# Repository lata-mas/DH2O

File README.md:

# Dispositivo H2O

Este dispositivo se realizó gracias al apoyo del proyecto UNAM-PAPIIT IT103023.

Este dispositivo se desarrollo con el objetivo de medir la cantidad de agua que se consume en un edificio y poder implementar medidas para evitar consumos excesivos de este valioso recurso.

El dispositivo funciona con un módulo NodeMCU Lolin V3→ESP8266-12E, permitiendo interpretar los datos que recolecta el sensor YF-S201 (sensor de caudal de agua), el microcontrolador  permite interpretar datos y después enviarlos a través de Wifi a una plataforma de imternet. La ventaja más significativa es precisamente esa, que el módulo tiene wifi, permitiendo que pueda enviar datos en tiempo real a diferentes plataformas de visualización, ademas de su reducido tamaño.

A continuación se muestra el esquema general del dispositivo y algunos de sus componetes principales:

1. Sensor de caudal
2. Divisor de voltaje
3. LM324

[Diagrama electrico](https://github.com/Dispositivos-Edificio-Bioclimatico/DH2O/blob/master/Diagramas/DispositivoH2O1Esquem%C3%A1tico.pdf)

## 1. Elementos del repositorio
-  #### En [**docs**](https://github.com/Dispositivos-Edificio-Bioclimatico/DH2O/tree/master/Documentacion) encontramos
	-  Lista de materiales y costos
	-  Manual de operación
	-  Fichas técnicas o datasheet de los módulos, sensores y componentes usados
	- Documento de errores, soluciones y recomendaciones

-  #### En [**diagramas**](https://github.com/Dispositivos-Edificio-Bioclimatico/DH2O/tree/master/Diagramas) encontramos
	- Pictograma de conexión
	- Esquemático de conexión
	
-  #### En [**codigo**](https://github.com/Dispositivos-Edificio-Bioclimatico/DH2O/tree/master/codigo) encontramos
	- Códigos completos
	- Librerías a usar.
	- Explicación.

-  #### En [**Imagenes**](https://github.com/Dispositivos-Edificio-Bioclimatico/Sistema_medicion_apertura_ventanas/tree/main/notebook) encontramos
	-  Imagenes usadas en el repositorio

-  #### En [**carcasa**](https://github.com/Dispositivos-Edificio-Bioclimatico/DH2O/tree/master/Diagramas) encontramos
	-  Planos CAD
	-  Archivos de diseño CAD
	-  Archivos STL para impresión 3D

### 2 Sobre los autores

|Nombre|Instituto/Organización|Email|
| ------------ | ------------ | ------------ |
|Luis Fernando De Olarte Delgado|UTEZ|ferdeod16@gmail.com|
|Marco Antonio Morales Lagunes|UTEZ|marcostony001@gmail.com|
|Julio César Landa López|UTEZ|landajulioc@gmail.com|
|Miguel Ángel Gaspar|ITZ|miguel97gaz@gmail.com|
|Escobar Escobar José Williams|ITE|escobarescobarwilliams@gmail.com|
|Guillermo Barrios del Valle|IER-UNAM|gbv@ier.unam.mx|
|Guillermo Ramírez Zúñiga|IER-UNAM|guraz@ier.unam.mx|
|Giovanni Velazquez Avilez||velazquezgio96@gmail.com|
|José Diego Salgado Nieto||salgadojosediego@gmail.com|

------------

# 3 Alcance

El dispositivo H2O tiene como alcance, en esta etapa, contar con toda la documentación necesaria para ser replicado de manera eficaz y eficientemente, después de ser trabajado por un grupo de personas se espera que el proyecto tenga todo lo que se necesita para que otras personas puedan entender el funcionamiento y requisitos de operación.

------------

### 4 Contacto primario

**Inv. A tiempo completo:** Dr. Guillermo Barrios del Valle

**Email:** gbv@ier.unam.mx

**Posdoc.:** Dr. Guillermo Ramírez Zúñiga

**Email:** guraz@ier.unam.mx

### Colaboradores

**Nombre:** Luis Fernando De Olarte Delgado

**Instituto:** Universidad Tecnológica Emiliano Zapata (UTEZ)

**Email:** ferdeod16@gmail.com

**Nombre:** Marco Antonio Morales Lagunes

**Instituto:** Universidad Tecnológica Emiliano Zapata (UTEZ)

**Email:** marcostony001@gmail.com

**Nombre:** Julio César Landa López

**Instituto:** Universidad Tecnológica Emiliano Zapata (UTEZ)

**Email:** landajulioc@gmail.com

**Nombre:** Miguel Ángel Gaspar

**Instituto:** Instituto Tecnológico de Zacatepec (ITZ)

**Email:** miguel97gaz@gmail.com

**Nombre:** Escobar Escobar José Williams

**Instituto:** Instituto Tecnológico de Ensenada (ITE)

**Email:** escobarescobarwilliams@gmail.com

**Nombre:** Salgado Nieto josé Diego
**Insituto** Universidad Tecnológica Emiliano Zapata (UTEZ)
**Email:** salgadojosediego@gmail.com

#### 5 Seguimiento de actividades del dispositivo H2O

|**Actividad**|**Tiempo estimado de ejecución**|**Referenciación**|
| :------------: | :------------: | :------------: |
|**1. Revisión de documentos existentes necesarios para operarlo de acuerdo a la CHECK-LIST**|2 h|[**°Documentación**](https://github.com/Dispositivos-Edificio-Bioclimatico/SensorH2O/tree/master/Documentacion) |
|   |   |   |
|**2. Verificar si cuenta con los materiales requeridos**|1/2 h|[**Materiales**](https://github.com/Dispositivos-Edificio-Bioclimatico/DH2O/tree/master/Documentacion/Materiales)|
|   |   |   |
|**3. Imprimir la carcasa en 3D (3 PARTES)**|16 h|[**Archivos STL**](https://github.com/Dispositivos-Edificio-Bioclimatico/DH2O/tree/master/carcasa)|
|   |   |   |
|**4. Leer el manual de operación para entender lo que se hará**|1 h|[**Manual**](https://github.com/Dispositivos-Edificio-Bioclimatico/DH2O/blob/master/Documentacion/Manuales/ManualDeOperacion.md)|
|   |   |   |
|**5. Entender los diagramas de conexión**|1/2 h|[**Diagramas**](https://github.com/Dispositivos-Edificio-Bioclimatico/DH2O/blob/master/Diagramas/H2O-Esquem%C3%A1tico_2023ver2-KiCad.pdf)|
|   |   |   |
|**6. Descargar e instalar el código completo (son 5 .py)**|1/2 h|[**Código H2O**](https://github.com/Dispositivos-Edificio-Bioclimatico/DH2O/tree/master/codigo)|
|   |   |   |
|**7. Ejecutar el código como primera prueba y asegurarse que funciona**|   |   |
|   |   |   |
|**8. Montar el dispositivo en el lugar requerido**|1 h|   |
|   |   |   |
|**9. Dejarlo operando durante 24 horas como prueba "Burn it"**|24 h|   |
|   |   |   |
|**10. Tiempo total apróximado:**|**3 días**|Dependerá de la habilidad y conocimientos que se tengan, puede llevar menos tiempo o más|

------------

### Thingsboard

Dashboard del dispositivo H2O en la plataforma de Thingsboard:

Miguel_H2O

Las credenciales para tener acceso se deberán solicitar con alguno de los doctores.

La web (Dashboard) se encuentra aquí:

[**Miguel_H2O**](http://iot.ier.unam.mx:8080/dashboard/5825dc60-059e-11eb-9c3f-d1ead9980bc3?publicId=0e7066c0-6e70-11e8-b1f3-991d62d050bd)

------------

# 6 Bibliografía

[1] Open Know-How
https://app.standardsrepo.com/MakerNetAlliance/OpenKnowHow/src/branch/master/1#a40dfa47-8bff-4e28-9338-3f808ddfe6ae

[2] Github
https://github.com/

[3] EasyEDA
https://easyeda.com/editor

[4] Fritzing
https://fritzing.org/

[5] DILLINGER
https://dillinger.io/

[6] M Editor.md
https://pandao.github.io/editor.md/en.html

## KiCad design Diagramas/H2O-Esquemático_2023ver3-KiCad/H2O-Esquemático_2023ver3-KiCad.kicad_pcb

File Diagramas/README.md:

##Diargramas del DH2O

En esta carpeta se presentan los diagramas.

Todo aquel documento qque represente como se construyó el dispositivo, diagramas de conexión, diagramas esequematicos y documentos CAD para su carcasa.
Los diagramas fueron realizados con el software libre KIcad, las carpetas presentan versiones de esquematicos y de pbc que muestran distintas formas de alimentación. Ambas versiones son funcionales, queda a elección del usuario cual usar.

En los directorios es posible encontrr los archivos gerber correspondientes para su  fabricación en PCB.

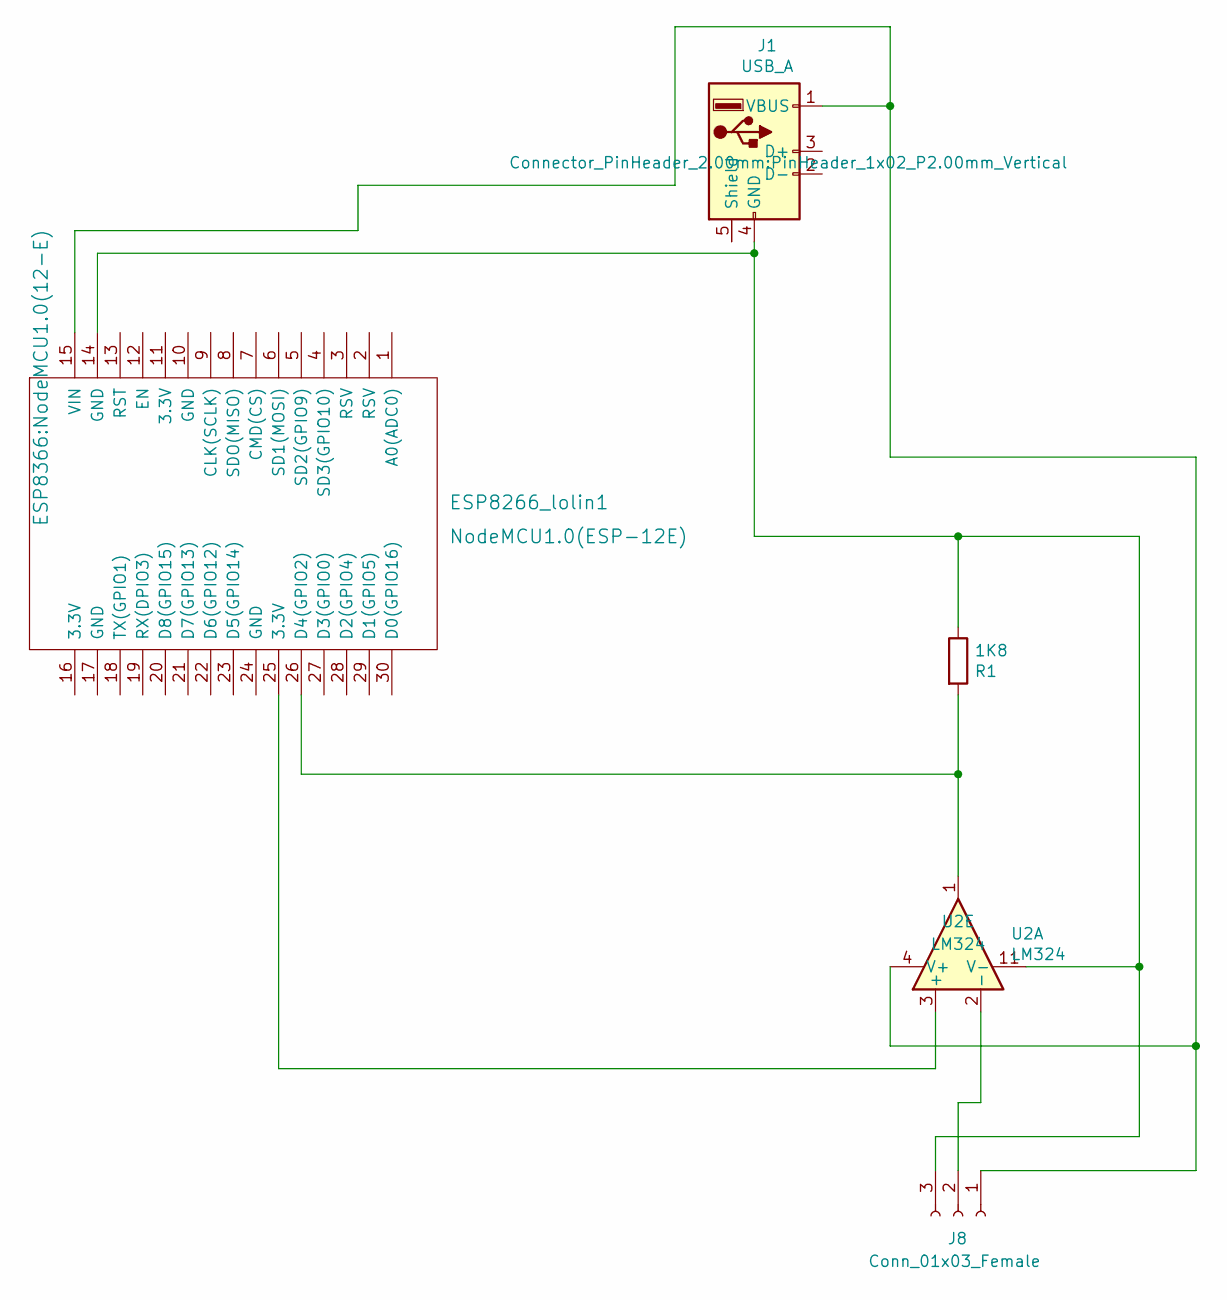
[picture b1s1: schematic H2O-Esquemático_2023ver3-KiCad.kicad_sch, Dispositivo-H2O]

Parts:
1K8: R1; R_Axial_DIN0207_L6.3mm_D2.5mm_P10.16mm_Horizontal
ESP8266_lolin1: NodeMCU1.0(ESP-12E); NodeMCU1.0(12-E)
J1: USB_A; PinHeader_1x02_P2.00mm_Vertical
J8: Conn_01x03_Female; TerminalBlock_4Ucon_1x03_P3.50mm_Vertical
U2: LM324; DIP-14_W7.62mm

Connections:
unnamed: 1K8.1, ESP8266_lolin1.14 (GND), J1.4 (GND), J8.3, U2.11 (V-)
unnamed: 1K8.2, ESP8266_lolin1.26 (D4(GPIO2)), U2.1
unnamed: ESP8266_lolin1.15 (VIN), J1.1 (VBUS), J8.1, U2.4 (V+)
unnamed: ESP8266_lolin1.25 (3.3V), U2.3 (+)
unnamed: J8.2, U2.2 (-)

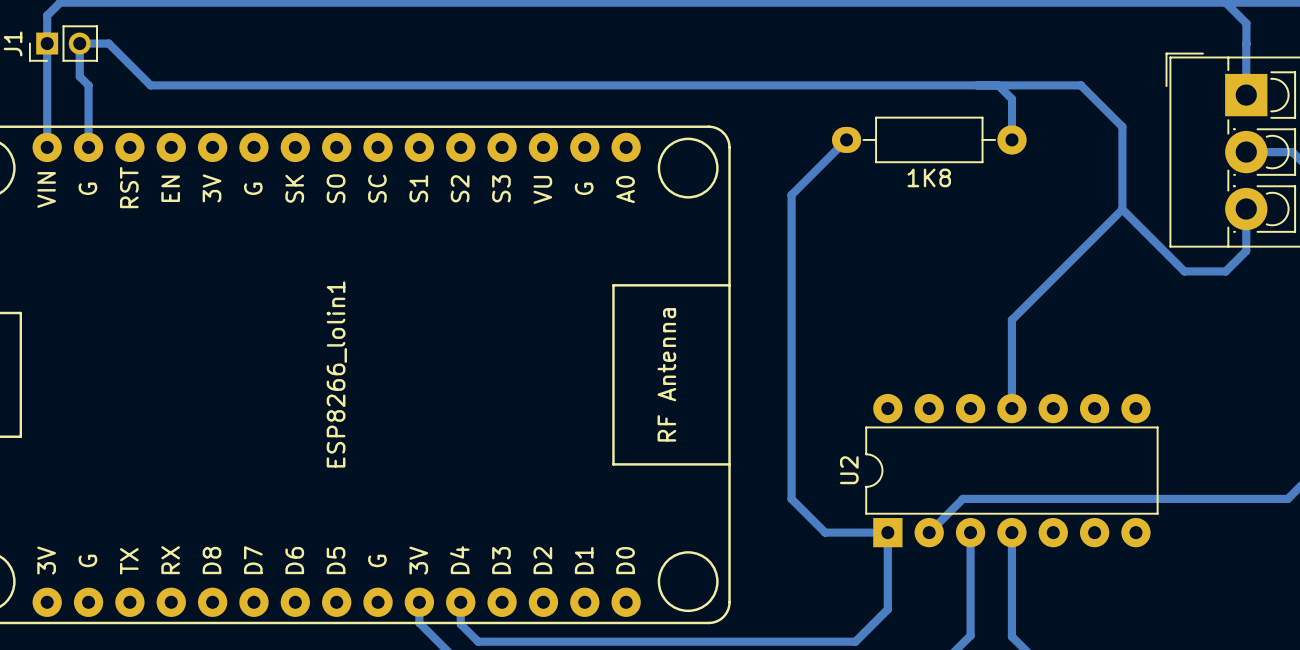
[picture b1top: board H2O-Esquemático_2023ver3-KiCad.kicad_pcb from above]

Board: 2 copper layers, 5 parts (0 on the bottom side), 5 nets.

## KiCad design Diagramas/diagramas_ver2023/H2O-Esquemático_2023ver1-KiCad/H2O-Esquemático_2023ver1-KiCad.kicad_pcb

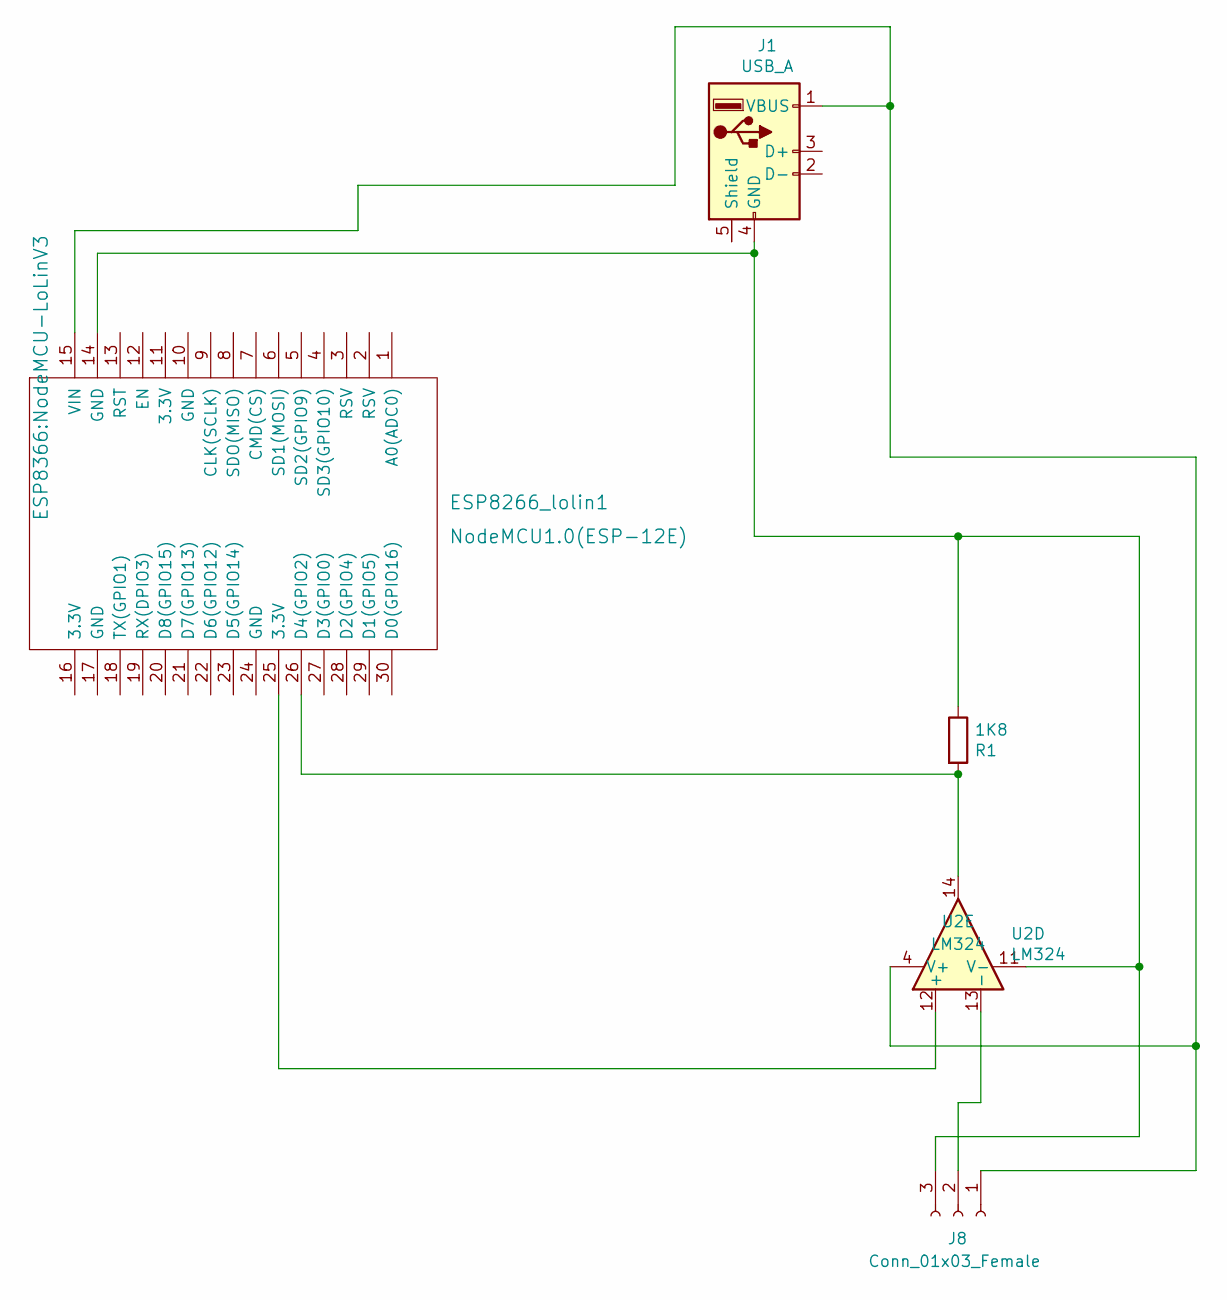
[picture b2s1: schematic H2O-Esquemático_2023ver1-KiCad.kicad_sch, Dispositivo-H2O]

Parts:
1K8: R1; R_Axial_DIN0207_L6.3mm_D2.5mm_P10.16mm_Horizontal
ESP8266_lolin1: NodeMCU1.0(ESP-12E); NodeMCU-LoLinV3
J1: USB_A; PinHeader_1x04_P1.27mm_Horizontal
J8: Conn_01x03_Female; TerminalBlock_Altech_AK300-3_P5.00mm
U2: LM324; DIP-14_W7.62mm

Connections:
unnamed: ESP8266_lolin1.25 (3.3V), U2.12 (+)
unnamed: 1K8.2, ESP8266_lolin1.26 (D4(GPIO2)), U2.14
unnamed: ESP8266_lolin1.15 (VIN), J1.1 (VBUS), J8.1, U2.4 (V+)
unnamed: 1K8.1, ESP8266_lolin1.14 (GND), J1.4 (GND), J8.3, U2.11 (V-)
unnamed: J8.2, U2.13 (-)

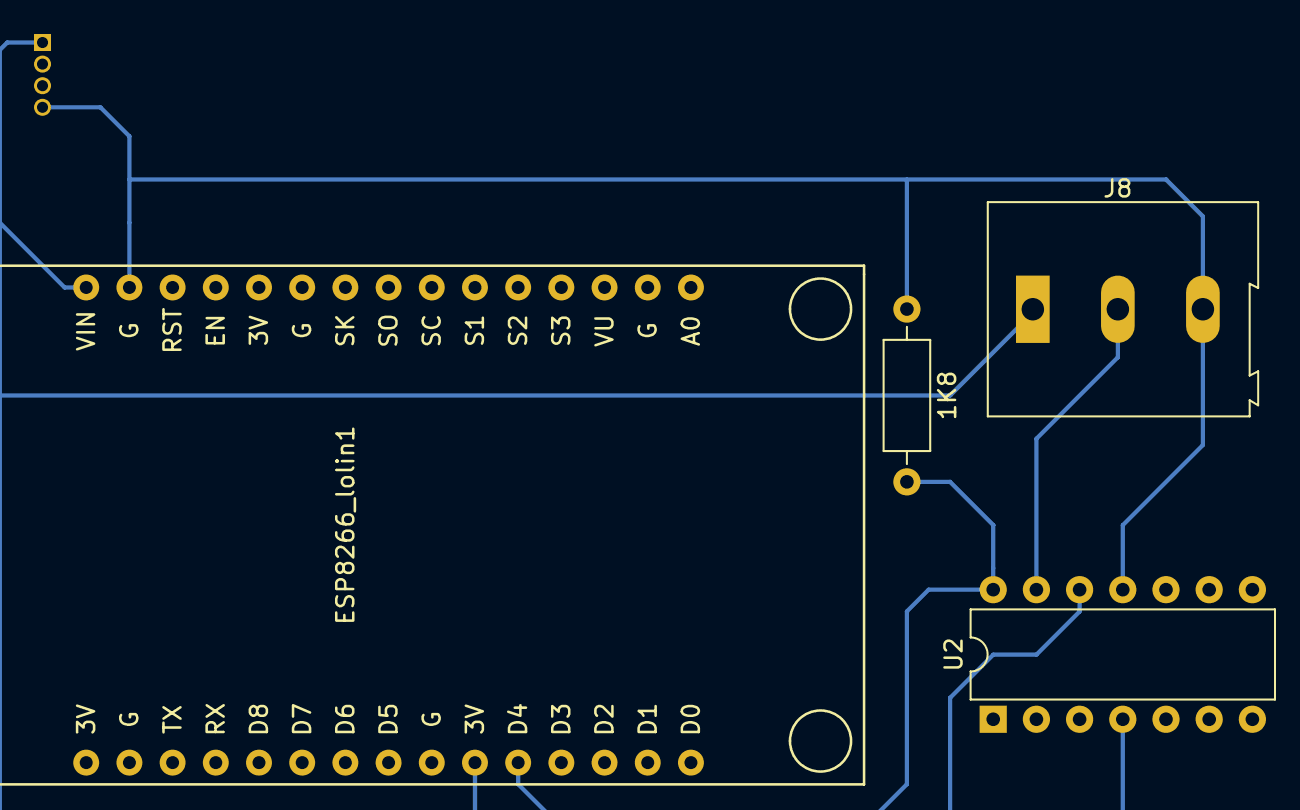
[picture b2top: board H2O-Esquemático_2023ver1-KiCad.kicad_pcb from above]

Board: 2 copper layers, 5 parts (1 on the bottom side), 5 nets.

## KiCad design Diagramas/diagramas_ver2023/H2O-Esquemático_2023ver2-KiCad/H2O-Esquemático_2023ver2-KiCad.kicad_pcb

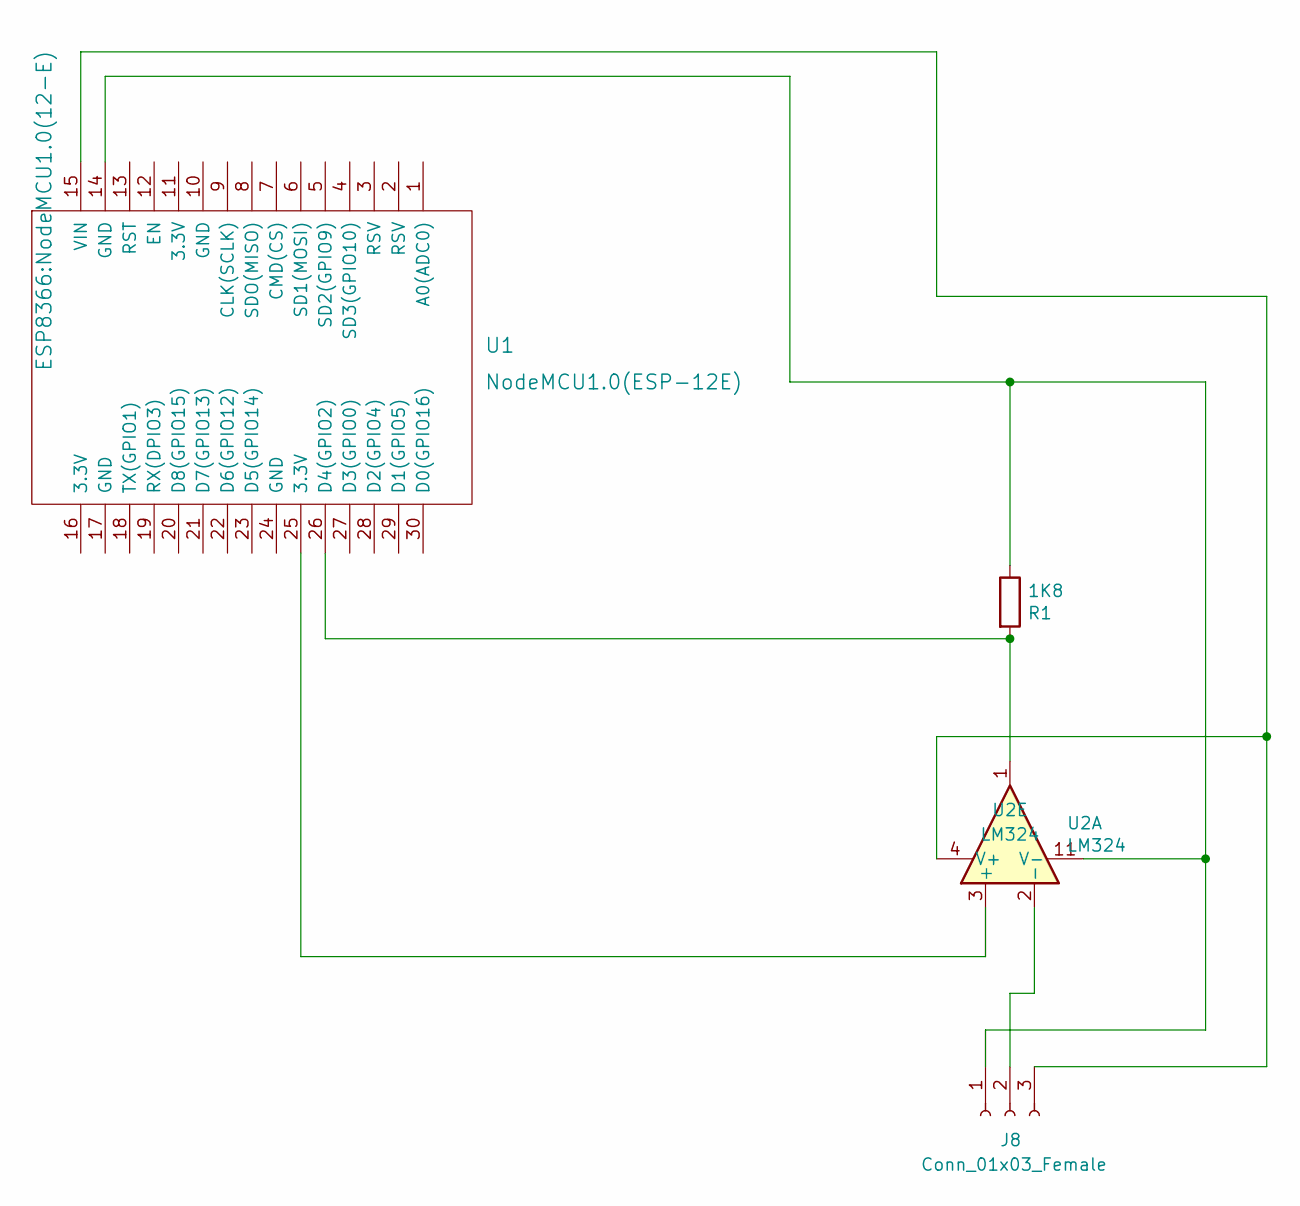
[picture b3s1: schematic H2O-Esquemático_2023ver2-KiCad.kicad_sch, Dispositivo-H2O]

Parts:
1K8: R1; R_Axial_DIN0207_L6.3mm_D2.5mm_P15.24mm_Horizontal
J8: Conn_01x03_Female; TerminalBlock_Altech_AK300-3_P5.00mm
U1: NodeMCU1.0(ESP-12E); NodeMCU1.0(12-E)
U2: LM324; DIP-14_W7.62mm

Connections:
unnamed: 1K8.1, J8.1, U1.14 (GND), U2.11 (V-)
unnamed: 1K8.2, U1.26 (D4(GPIO2)), U2.1
unnamed: J8.2, U2.2 (-)
unnamed: J8.3, U1.15 (VIN), U2.4 (V+)
unnamed: U1.25 (3.3V), U2.3 (+)

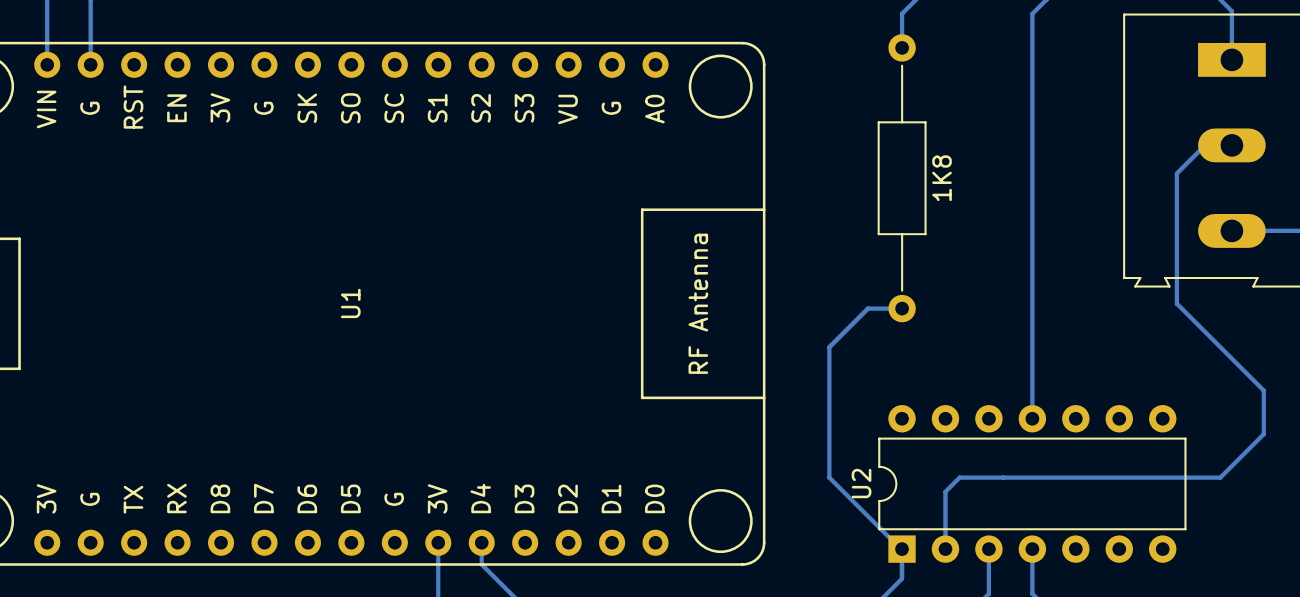
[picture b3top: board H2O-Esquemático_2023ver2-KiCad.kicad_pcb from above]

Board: 2 copper layers, 4 parts (0 on the bottom side), 5 nets.

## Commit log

2020-01-30 Primera versión funcional del código
2020-01-30 Código comentado
2020-01-31 Código funcional para la medición de dos sensores con una tarjerta
2020-02-05 Add files via upload
    función modular para ecuaciones del sensor agragada
2020-02-05 funciones modulares de empaquetamiento de datos agregadas
2020-02-05 Reacomodo de código se añade etiquetas para publicar en thingsboard
2020-02-05 Código modular y funcional para 1 sensor
2020-02-06 Se eliminó calculo del flujo, sin volver modular el conteo digital
2020-02-06 Se agrego una clase, aun tiene detalles el código
2020-02-06 Clase para medir volumen de agua
2020-02-07 funcional varios sensores
2020-02-07 eliminando mains innecesarios
2020-02-07 Versión 0.6 funcional para 1 o varios sensores
2020-02-07 No publica ceros
2020-02-07 Publica por persona
2020-02-10 Explicación de las funciones
2020-02-10 Reacomodo de la clase conteo para simplificar main
2020-02-10 Código modular que publica por persona
2020-02-10 Correción de etiquetas
2020-02-12 Se agrega constante del sensor
2020-02-13 Publicación de constante como atributo
2020-02-13 Optimización de algunas clases
2020-02-14 Comparación de sensor con estado anterior
2020-02-17 Publica constante del sensor
2020-02-18 Optimización de metodos
2020-04-27 Diagramas
2020-12-28 agregue un mensaje para MA
2021-01-06 agregre
2021-01-27 Carpetas completas
2021-01-27 Modifiqué el README
2021-01-27 Borre el swp vacio
2021-01-27 Borre el README de prueba
2021-01-27 Este es el README modelo
2021-01-27 Mofique links del README
2021-01-27 Modifique el README
2021-01-27 Modifique links
2021-02-17 No va en esta carpeta
2021-02-17 modifiqué el nombre
2021-02-22 Modifiqué texto
2021-02-22 Modifiqué espacios en texto
2021-03-08 Modifiqué
2021-03-11 Modifiqué el MO
2021-03-16 Agregué datos de Thingsboard
2021-03-18 Actualicé el Manual de operación
2021-05-21 reduje el c'odigo de main8s y lo pas'e a main.py
2021-05-24 Agregué un código
2021-06-03 rama de 5 sensores para la historia
2021-06-03 rama principal para 1 sensor de agua
2021-06-16 todo actualizado a 1S
2021-08-05 actualicé
2021-08-06 agregué carpeta
2022-02-24 actualizacion
    actualizacion
2022-03-04 agregue
2022-03-04 actualice
2023-01-30 Se elimina el divisor de voltaje en esta versión
2023-01-30 Modificación enero 2023
2023-01-30 Modificado en enero 2023
2023-04-28 v1.0.0
2023-05-04 readme act
